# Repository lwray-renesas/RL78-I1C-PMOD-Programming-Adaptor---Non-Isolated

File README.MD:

# Project Title

RL78/I1C PMOD Programming Adaptor - Non-Isolated

## Description

This piece of hardware alows connection between an E2-Lite and any of the RL78/I1C Metering PMOD's.
It is not isolated and care should be taken to ensure no live connection to mains or other high votlage sourec is present when connecting.

Gerbers, Schematics and BoM for the latest revision are included in the repository under the build directory.

## Getting Started

### Dependencies

* KiCad 7.0
* [Component Libraries](https://github.com/lwray-renesas/RL78-I1C-PMOD-Programming-Adaptor-KiCad-Libraries.)

## License

This project is licensed under the MIT License - see the LICENSE.md file for details

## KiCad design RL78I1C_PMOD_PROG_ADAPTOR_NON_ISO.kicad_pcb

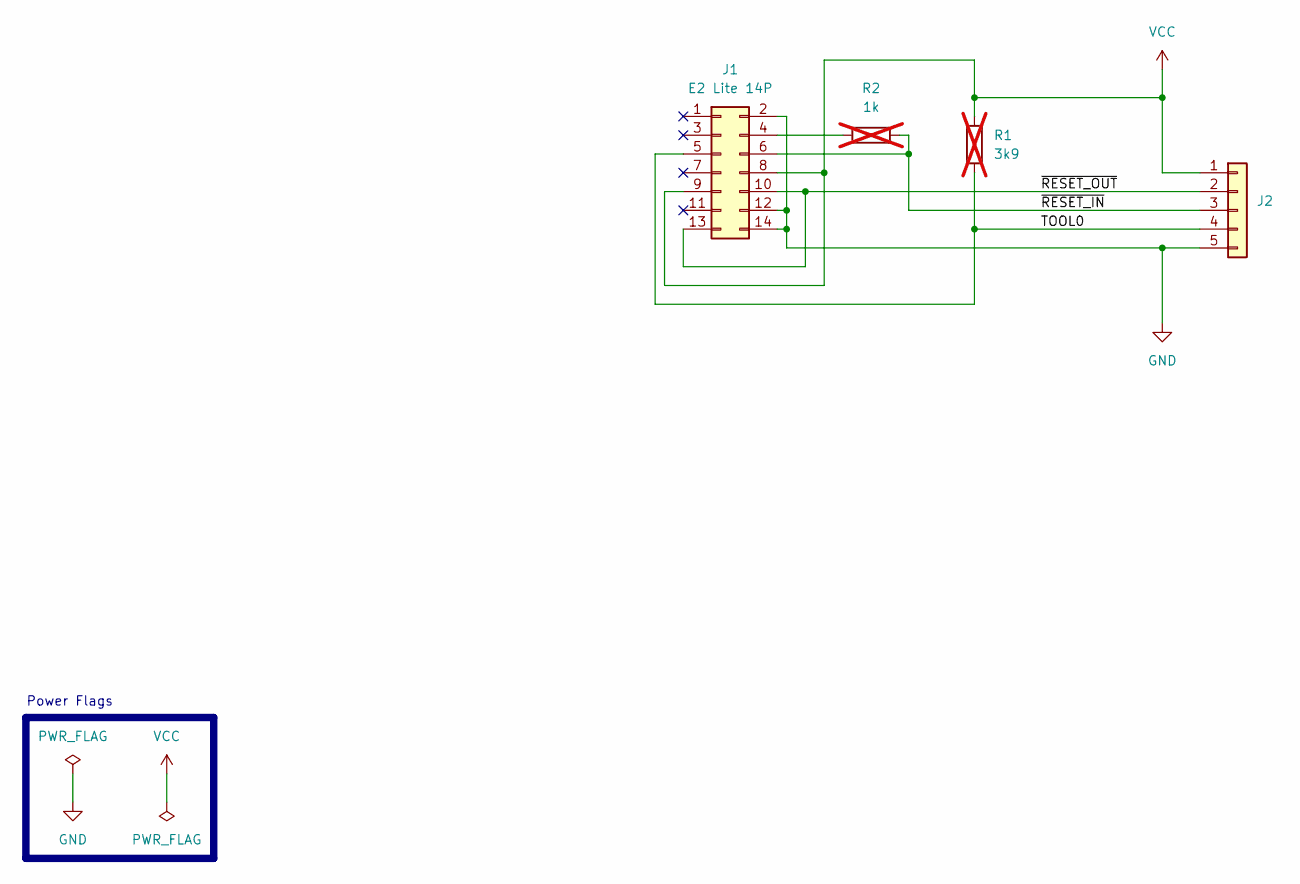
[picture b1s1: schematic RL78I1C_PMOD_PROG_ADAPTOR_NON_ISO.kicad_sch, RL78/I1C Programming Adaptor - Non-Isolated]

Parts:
J1: E2 Lite 14P; PinHeader_2x07_P2.54mm_Vertical; Manufacturer p/n N2514-6002-RB; Digikey p/n MHC14K-ND
J2: RL78/I1C 5P; PinHeader_1x05_P2.54mm_Vertical; Manufacturer p/n 61300511821; Digikey p/n 732-61300511821-ND
R1: 3k9; R_0603_1608Metric_Pad0.98x0.95mm_HandSolder; Manufacturer p/n RC0603FR-133K9L; Digikey p/n 13-RC0603FR-133K9LCT-ND; not fitted
R2: 1k; R_0603_1608Metric_Pad0.98x0.95mm_HandSolder; Manufacturer p/n RC0603FR-071KL; Digikey p/n 311-1.00KHRCT-ND; not fitted

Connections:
/TOOL0: J1.5, J2.4, R1.2
/~RESET_IN: J1.6, J2.3, R2.2
/~RESET_OUT: J1.10, J1.13, J2.2
GND: J1.2, J1.12, J1.14, J2.5
unnamed: J1.4, R2.1
VCC: J1.8, J1.9, J2.1, R1.1

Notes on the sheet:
Power Flags

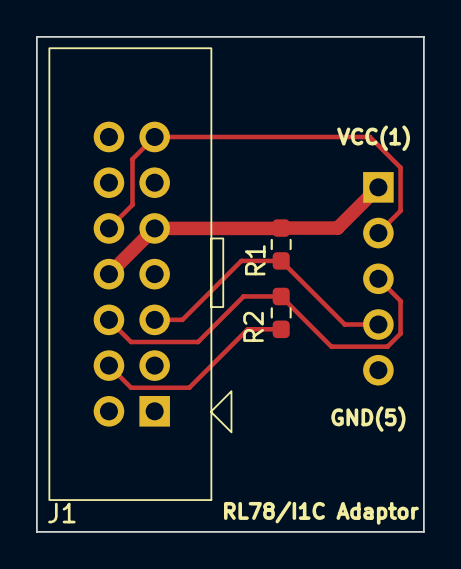
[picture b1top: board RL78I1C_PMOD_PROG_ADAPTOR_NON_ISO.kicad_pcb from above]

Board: 2 copper layers, 21.5 x 27.5 mm, 4 parts (1 on the bottom side), 6 nets.

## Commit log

2024-07-26 First commit.
2024-07-26 Updated readme with component library link.
2024-07-26 Updated broken link.
2024-10-22 Refreshed gerbers.
